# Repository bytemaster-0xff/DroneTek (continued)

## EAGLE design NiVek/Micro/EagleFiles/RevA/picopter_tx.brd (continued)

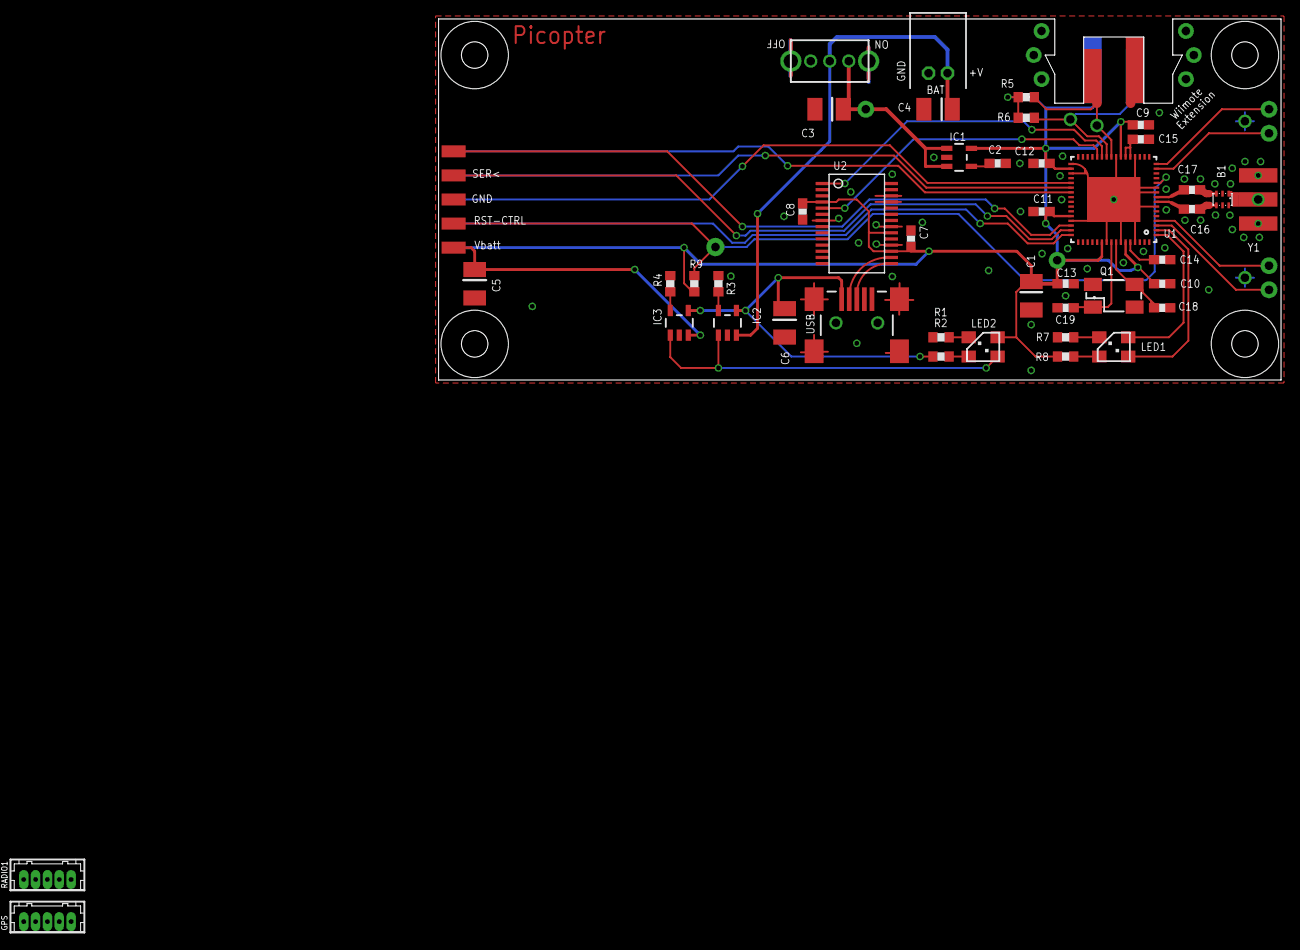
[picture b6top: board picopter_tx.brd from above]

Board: 2 copper layers, 88.9 x 38.1 mm, 53 parts (0 on the bottom side), 38 nets.

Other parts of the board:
U$1: MOCKQC
U$2: PICOPTER-LOGO
U$5, U$8: ARM-MOCK

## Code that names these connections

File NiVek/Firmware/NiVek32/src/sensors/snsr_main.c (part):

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	 * the file size smaller and you can immediately
	 * see what's hooked up to what
	 */
	/* PC10- L3GD20 Gyro */
	irqConfig.GPIO_Pin = GPIO_Pin_10;
	GPIO_Init(GPIOC, &irqConfig);
	SYSCFG_EXTILineConfig(EXTI_PortSourceGPIOC, EXTI_PinSource10);

	/* PA8- ITG3200/MPU6050 Gyro/Acc */
	irqConfig.GPIO_Pin = GPIO_Pin_8;
	GPIO_Init(GPIOA, &irqConfig);
	SYSCFG_EXTILineConfig(EXTI_PortSourceGPIOA, EXTI_PinSource8);

	/* PC3- BMP085-EOC */
	irqConfig.GPIO_Pin = GPIO_Pin_3;
	GPIO_Init(GPIOC, &irqConfig);
	SYSCFG_EXTILineConfig(EXTI_PortSourceGPIOC, EXTI_PinSource3);

	/* PB2- Sonar Echo/HC-SR04 */
	irqConfig.GPIO_Pin = GPIO_Pin_2;
	GPIO_Init(GPIOB, &irqConfig);
	SYSCFG_EXTILineConfig(EXTI_PortSourceGPIOB, EXTI_PinSource2);

	/* PB14- ADXL 345 */
	irqConfig.GPIO_Pin = GPIO_Pin_14;
	GPIO_Init(GPIOB, &irqConfig);
	SYSCFG_EXTILineConfig(EXTI_PortSourceGPIOB, EXTI_PinSource14);

	/* PB13- LSM303 Acc/Mag */
	irqConfig.GPIO_Pin = GPIO_Pin_13;
	GPIO_Init(GPIOB, &irqConfig);
	SYSCFG_EXTILineConfig(EXTI_PortSourceGPIOB, EXTI_PinSource13);
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
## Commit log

2017-12-30 move from svn
2017-12-30 working as a Win10UWP app (w/ DirectX)
2018-01-01 upgraded directx library to win10
2018-01-01 compiling firmware and groundstation
2020-10-26 protocol updates
2022-06-22 Bump Newtonsoft.Json
    Bumps [Newtonsoft.Json](https://github.com/JamesNK/Newtonsoft.Json) from 11.0.1-beta1 to 13.0.1.
    - [Release notes](https://github.com/JamesNK/Newtonsoft.Json/releases)
    - [Commits](https://github.com/JamesNK/Newtonsoft.Json/commits/13.0.1)
    ---
    updated-dependencies:
    - dependency-name: Newtonsoft.Json
2022-06-22 Bump Newtonsoft.Json
    Bumps [Newtonsoft.Json](https://github.com/JamesNK/Newtonsoft.Json) from 6.0.2 to 13.0.1.
    - [Release notes](https://github.com/JamesNK/Newtonsoft.Json/releases)
    - [Commits](https://github.com/JamesNK/Newtonsoft.Json/compare/6.0.2...13.0.1)
    ---
    updated-dependencies:
    - dependency-name: Newtonsoft.Json
2022-06-22 Bump Newtonsoft.Json in /NiVek/Software/GroundStation/FlightControls
    Bumps [Newtonsoft.Json](https://github.com/JamesNK/Newtonsoft.Json) from 6.0.2 to 13.0.1.
    - [Release notes](https://github.com/JamesNK/Newtonsoft.Json/releases)
    - [Commits](https://github.com/JamesNK/Newtonsoft.Json/compare/6.0.2...13.0.1)
    ---
    updated-dependencies:
    - dependency-name: Newtonsoft.Json
2022-06-22 Bump Newtonsoft.Json in /NiVek/Software/GroundStation/NiVek.Common
    Bumps [Newtonsoft.Json](https://github.com/JamesNK/Newtonsoft.Json) from 6.0.2 to 13.0.1.
    - [Release notes](https://github.com/JamesNK/Newtonsoft.Json/releases)
    - [Commits](https://github.com/JamesNK/Newtonsoft.Json/compare/6.0.2...13.0.1)
    ---
    updated-dependencies:
    - dependency-name: Newtonsoft.Json
2022-12-08 Bump Newtonsoft.Json
    Bumps [Newtonsoft.Json](https://github.com/JamesNK/Newtonsoft.Json) from 11.0.1-beta1 to 13.0.2.
    - [Release notes](https://github.com/JamesNK/Newtonsoft.Json/releases)
    - [Commits](https://github.com/JamesNK/Newtonsoft.Json/commits/13.0.2)
    ---
    updated-dependencies:
    - dependency-name: Newtonsoft.Json
